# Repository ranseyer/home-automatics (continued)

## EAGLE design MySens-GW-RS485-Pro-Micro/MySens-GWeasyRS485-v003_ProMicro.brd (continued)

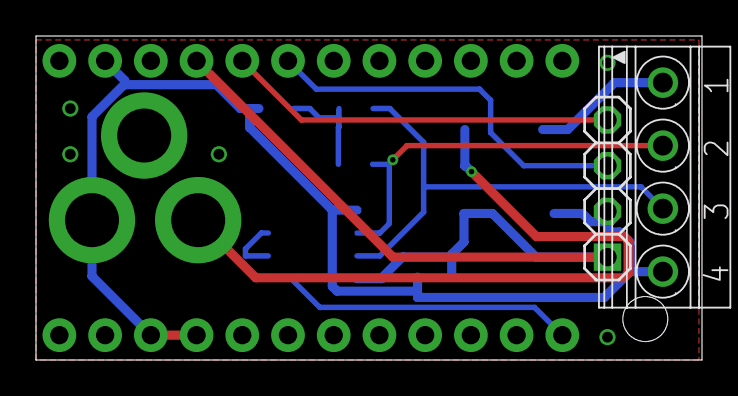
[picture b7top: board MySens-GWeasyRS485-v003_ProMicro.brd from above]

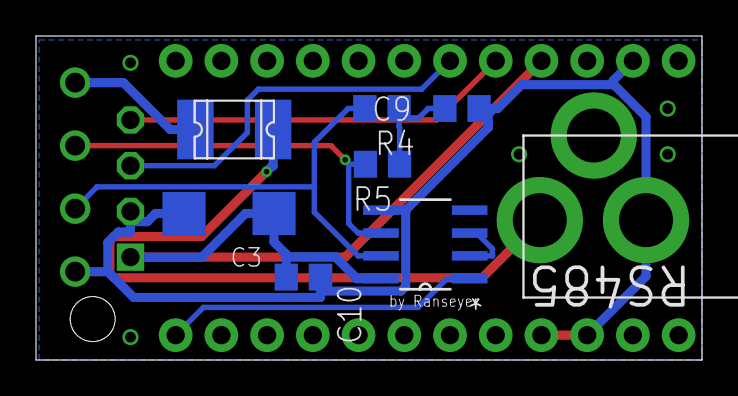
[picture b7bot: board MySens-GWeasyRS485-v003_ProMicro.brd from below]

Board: 2 copper layers, 37.0 x 18.0 mm, 11 parts (8 on the bottom side), 11 nets.
